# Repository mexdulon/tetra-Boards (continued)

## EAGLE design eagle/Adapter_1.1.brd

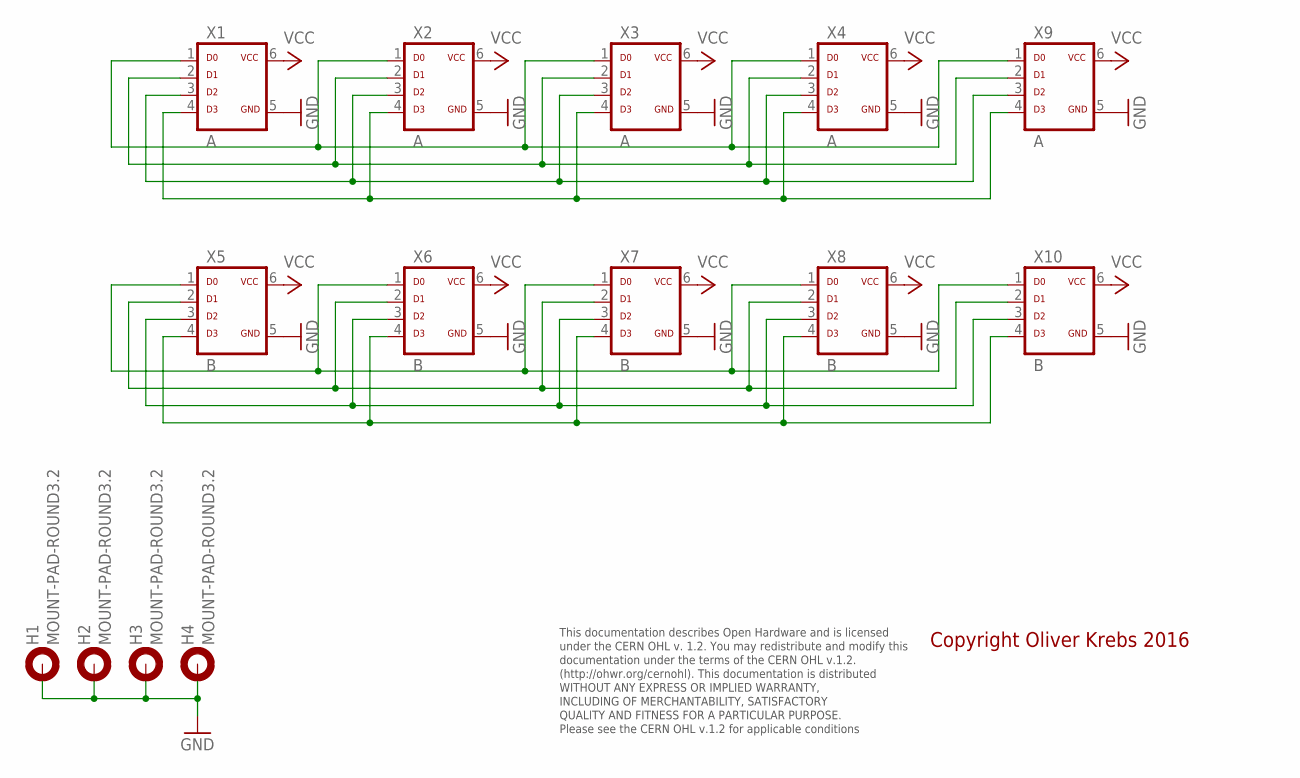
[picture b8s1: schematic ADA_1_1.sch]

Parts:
H1, H2, H3, H4: MOUNT-PAD-ROUND3.2; 3,2-PAD
X1, X2, X3, X4, X9: A; ML-6
X5, X6, X7, X8, X10: B; ML-6

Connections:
GND: H1.B3,2, H2.B3,2, H3.B3,2, H4.B3,2, X1.5, X2.5, X3.5, X4.5, X5.5, X6.5, X7.5, X8.5, X9.5, X10.5
unnamed: X1.1, X2.1, X3.1, X4.1, X9.1
unnamed: X1.2, X2.2, X3.2, X4.2, X9.2
unnamed: X1.3, X2.3, X3.3, X4.3, X9.3
unnamed: X1.4, X2.4, X3.4, X4.4, X9.4
unnamed: X5.1, X6.1, X7.1, X8.1, X10.1
unnamed: X5.2, X6.2, X7.2, X8.2, X10.2
unnamed: X5.3, X6.3, X7.3, X8.3, X10.3
unnamed: X5.4, X6.4, X7.4, X8.4, X10.4
VCC: X1.6, X2.6, X3.6, X4.6, X5.6, X6.6, X7.6, X8.6, X9.6, X10.6

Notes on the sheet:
This documentation describes Open Hardware and is licensed under the CERN OHL v. 1.2. You may redistribute and modify this documentation under the terms of the CERN OHL v.1.2. (http://ohwr.org/cernohl). This documentation is distributed WITHOUT ANY EXPRESS OR IMPLIED WARRANTY, INCLUDING OF MERCHANT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
Copyright Oliver Krebs 2016

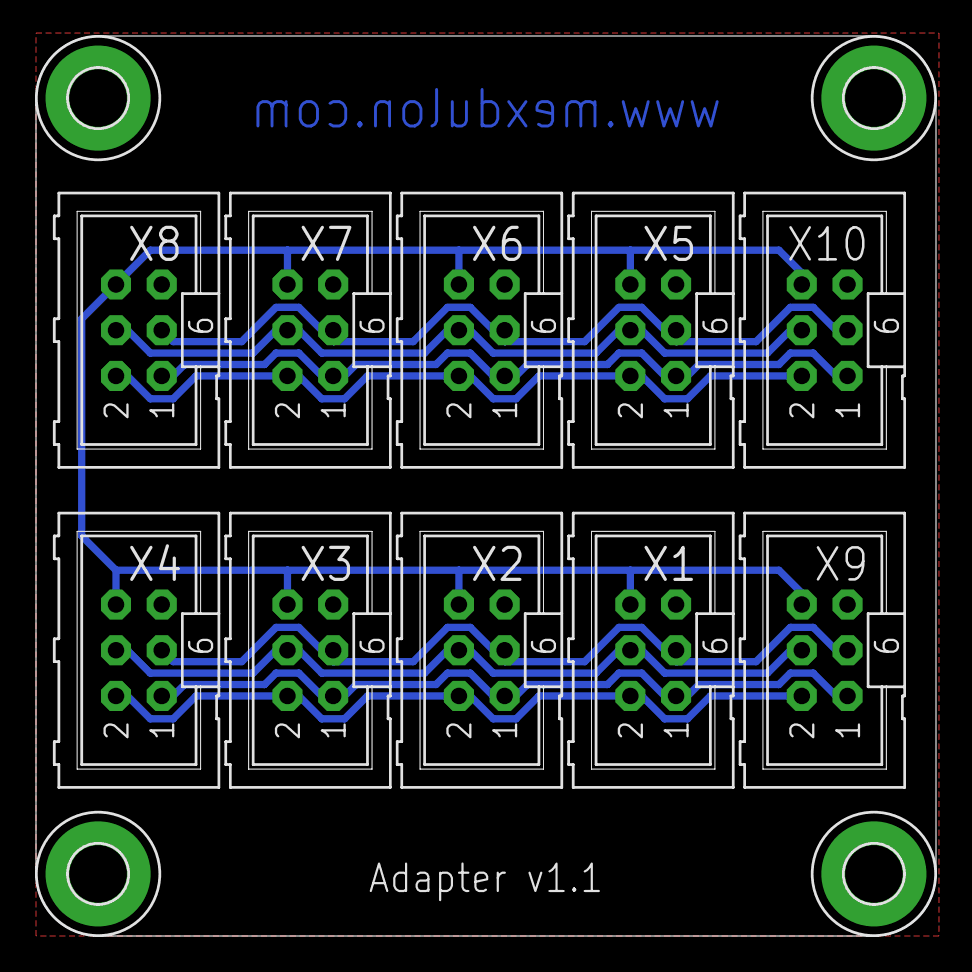
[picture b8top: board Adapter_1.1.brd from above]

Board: 2 copper layers, 50.0 x 50.0 mm, 14 parts (0 on the bottom side), 10 nets.
